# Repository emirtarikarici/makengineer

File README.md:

# MAKEngineer 2022
This repo is my outputs from MAKEngineer Certificate Program, organized by OPENFAB @ Özyeğin University

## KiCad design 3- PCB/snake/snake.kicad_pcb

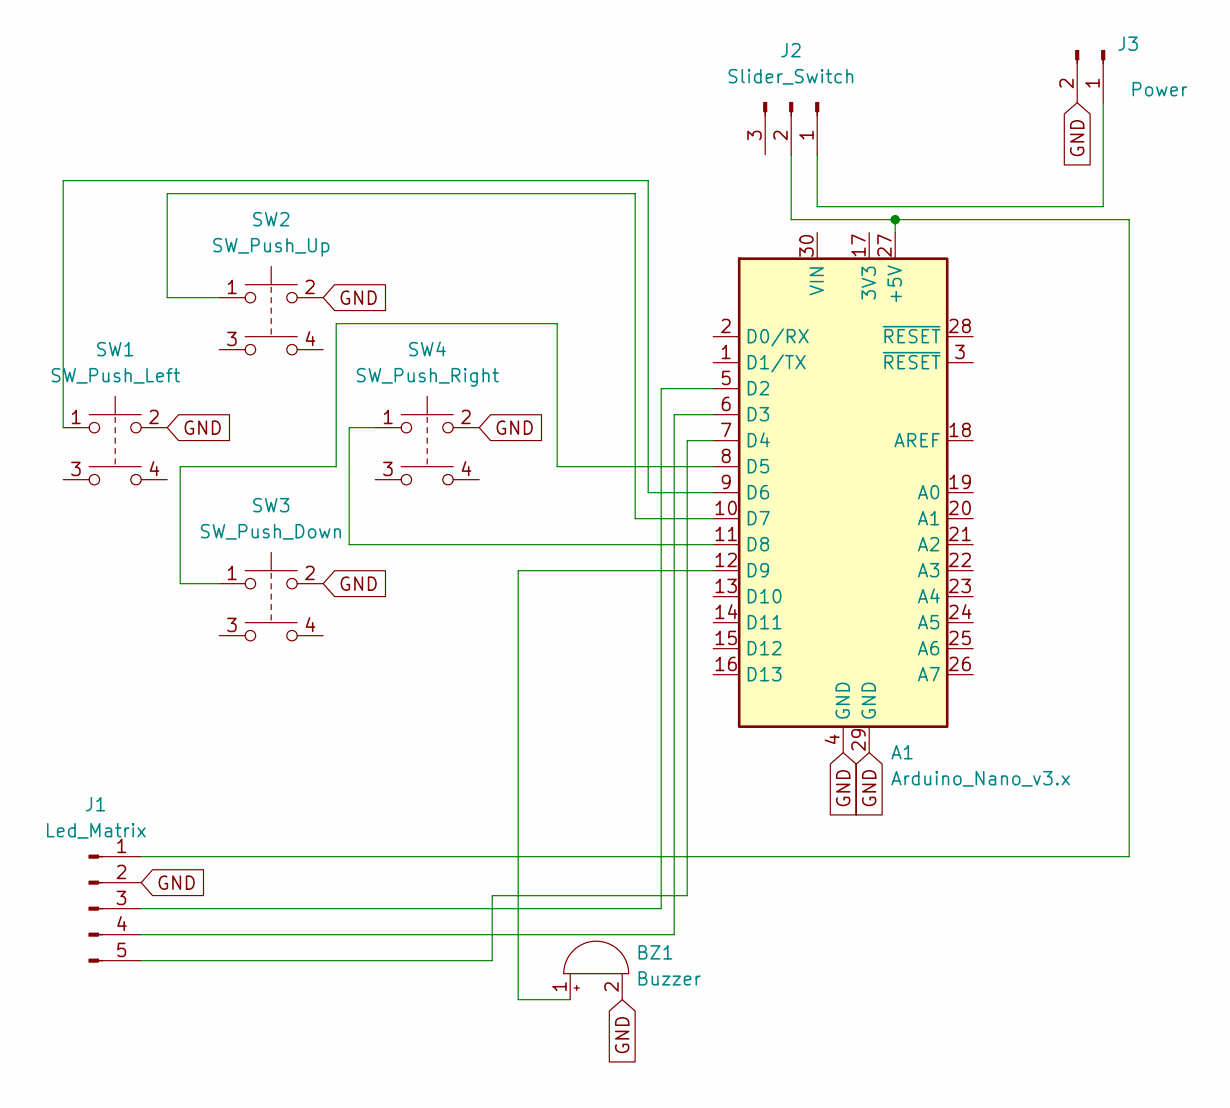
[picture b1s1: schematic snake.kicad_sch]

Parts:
A1: Arduino_Nano_v3.x; Arduino_Nano
BZ1: Buzzer; Buzzer_12x9.5RM7.6
J1: Led_Matrix; PinHeader_1x05_P2.54mm_Vertical
J2: Slider_Switch
J3: Power; PinHeader_1x02_P2.54mm_Vertical
SW1: SW_Push_Left
SW2: SW_Push_Up
SW3: SW_Push_Down
SW4: SW_Push_Right

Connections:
GND: A1.4 (GND), A1.29 (GND), BZ1.2 (+), J1.2, J3.2, SW1.2, SW2.2, SW3.2, SW4.2
unnamed: A1.5 (D2), J1.3
unnamed: A1.6 (D3), J1.4
unnamed: A1.7 (D4), J1.5
unnamed: A1.8 (D5), SW3.1
unnamed: A1.9 (D6), SW1.1
unnamed: A1.10 (D7), SW2.1
unnamed: A1.11 (D8), SW4.1
unnamed: A1.12 (D9), BZ1.1 (-)
unnamed: A1.27 (+5V), J1.1, J2.2
unnamed: J2.1, J3.1

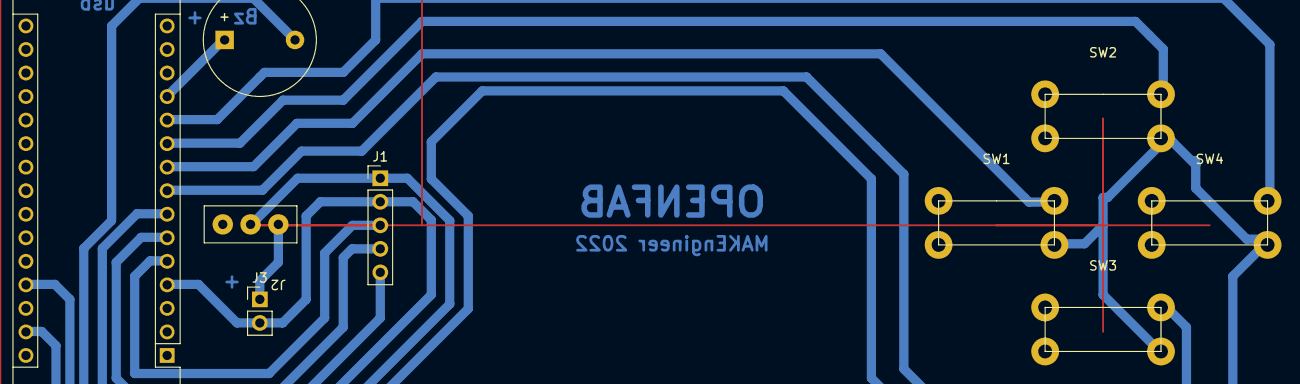
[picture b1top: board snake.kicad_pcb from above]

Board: 2 copper layers, 9 parts (0 on the bottom side), 11 nets.

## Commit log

2022-04-23 "upload"
